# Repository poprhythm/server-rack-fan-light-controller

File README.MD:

# Server Rack Fan & Light Controller PCB
Provides control for server rack electronics using ESP32.

## Firmware

ESP32 firmware with temperature-controlled fans and MQTT monitoring is available in the [firmware/](./firmware/) directory.

PCB Mounted Components

- J1:	Front Connections - 8 pin Dupont connector
- J2:	Back Connections - 8 pin Dupont connector
- J3:	Barrel Jack for 24V
- J4:	[TMP32](https://www.amazon.com/dp/B08BFY91ZW)
- Q1, Q2:	[RFP30N06LE](https://www.digikey.com/en/products/detail/onsemi/RFP30N06LE/458769)
- R1, R2:	10K
- U1:	[ESP32 - ESP-WROOM-32 ESP-32S](https://www.amazon.com/ESP-WROOM-32-Development-Microcontroller-Integrated-Compatible/dp/B08D5ZD528)
- U2:	[LM2596S-Module 24V to 12V](https://www.amazon.com/dp/B076H3XHXP)
- U3:	[LM2596S-Module 24V to 5V](https://www.amazon.com/dp/B076H3XHXP)

External Components

- [24V LED Light strips](https://www.amazon.com/dp/B0D454HJ8G)
- [12V Fans](https://www.amazon.com/dp/B07HC782D5)
- [Door Sensor](https://www.amazon.com/dp/B0B3D7BM4K)
- [Electrical Wire](https://www.amazon.com/dp/B0CN76J8KR)
- [Dupont Connectors](https://www.amazon.com/dp/B078RRPRQZ)

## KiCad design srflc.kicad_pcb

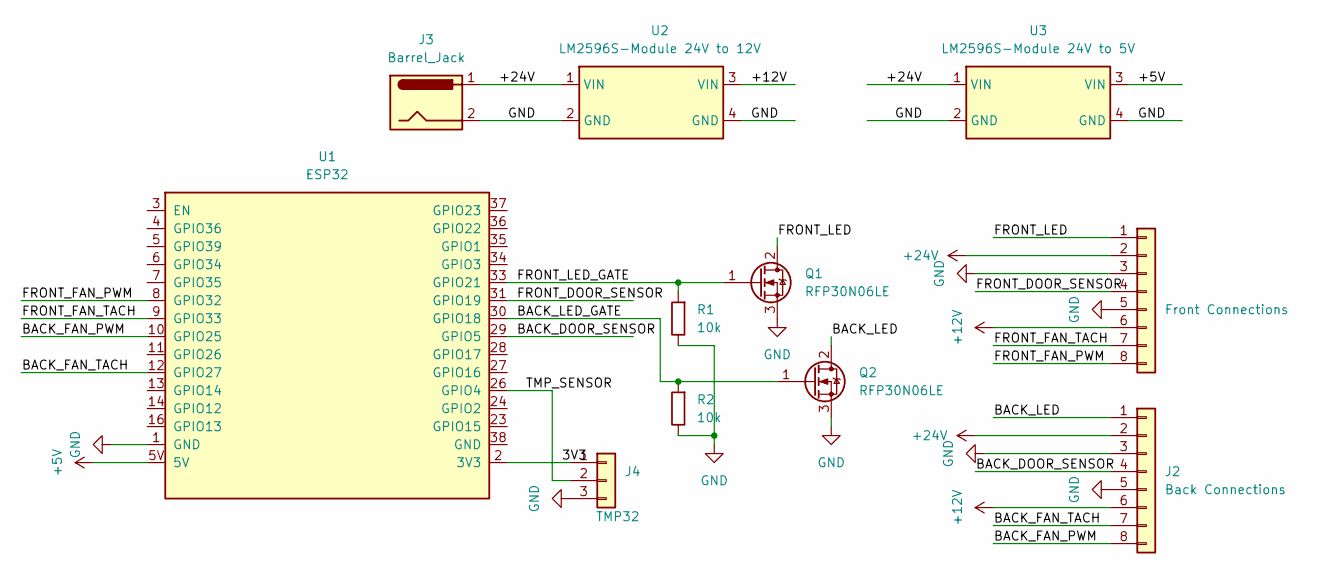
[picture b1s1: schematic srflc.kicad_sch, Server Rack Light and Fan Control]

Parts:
J1: Front Connections; PinHeader_1x08_P2.54mm_Horizontal
J2: Back Connections; PinHeader_1x08_P2.54mm_Horizontal
J3: Barrel_Jack; PinHeader_1x02_P2.54mm_Vertical
J4: TMP32; PinHeader_1x03_P2.54mm_Vertical
Q1, Q2: RFP30N06LE; PinHeader_1x03_P2.54mm_Vertical
R1, R2: 10k; R_Axial_DIN0207_L6.3mm_D2.5mm_P10.16mm_Horizontal
U1: ESP32; ESP32-C3-DevKitM-1
U2: LM2596S-Module 24V to 12V; LM2596 DC to DC High Efficiency Voltage Regulator 3.2-35V t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
U3: LM2596S-Module 24V to 5V; LM2596 DC to DC High Efficiency Voltage Regulator 3.2-35V t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

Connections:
+5V: U1.5V, U3.3 (VIN)
+12V: J1.6, J2.6, U2.3 (VIN)
+24V: J1.2, J2.2, J3.1, U2.1 (VIN), U3.1 (VIN)
/3V3: J4.1, U1.2 (3V3)
/BACK_DOOR_SENSOR: J2.4, U1.29 (GPIO5)
/BACK_FAN_PWM: J2.8, U1.10 (GPIO25)
/BACK_FAN_TACH: J2.7, U1.12 (GPIO27)
/BACK_LED: J2.1, Q2.2 (D)
/BACK_LED_GATE: Q2.1 (G), R2.1, U1.30 (GPIO18)
/FRONT_DOOR_SENSOR: J1.4, U1.31 (GPIO19)
/FRONT_FAN_PWM: J1.8, U1.8 (GPIO32)
/FRONT_FAN_TACH: J1.7, U1.9 (GPIO33)
/FRONT_LED: J1.1, Q1.2 (D)
/FRONT_LED_GATE: Q1.1 (G), R1.1, U1.33 (GPIO21)
/TMP_SENSOR: J4.2, U1.26 (GPIO4)
GND: J1.3, J1.5, J2.3, J2.5, J3.2, J4.3, Q1.3 (S), Q2.3 (S), R1.2, R2.2, U1.1 (GND), U2.2 (GND), U2.4 (GND), U3.2 (GND), U3.4 (GND)

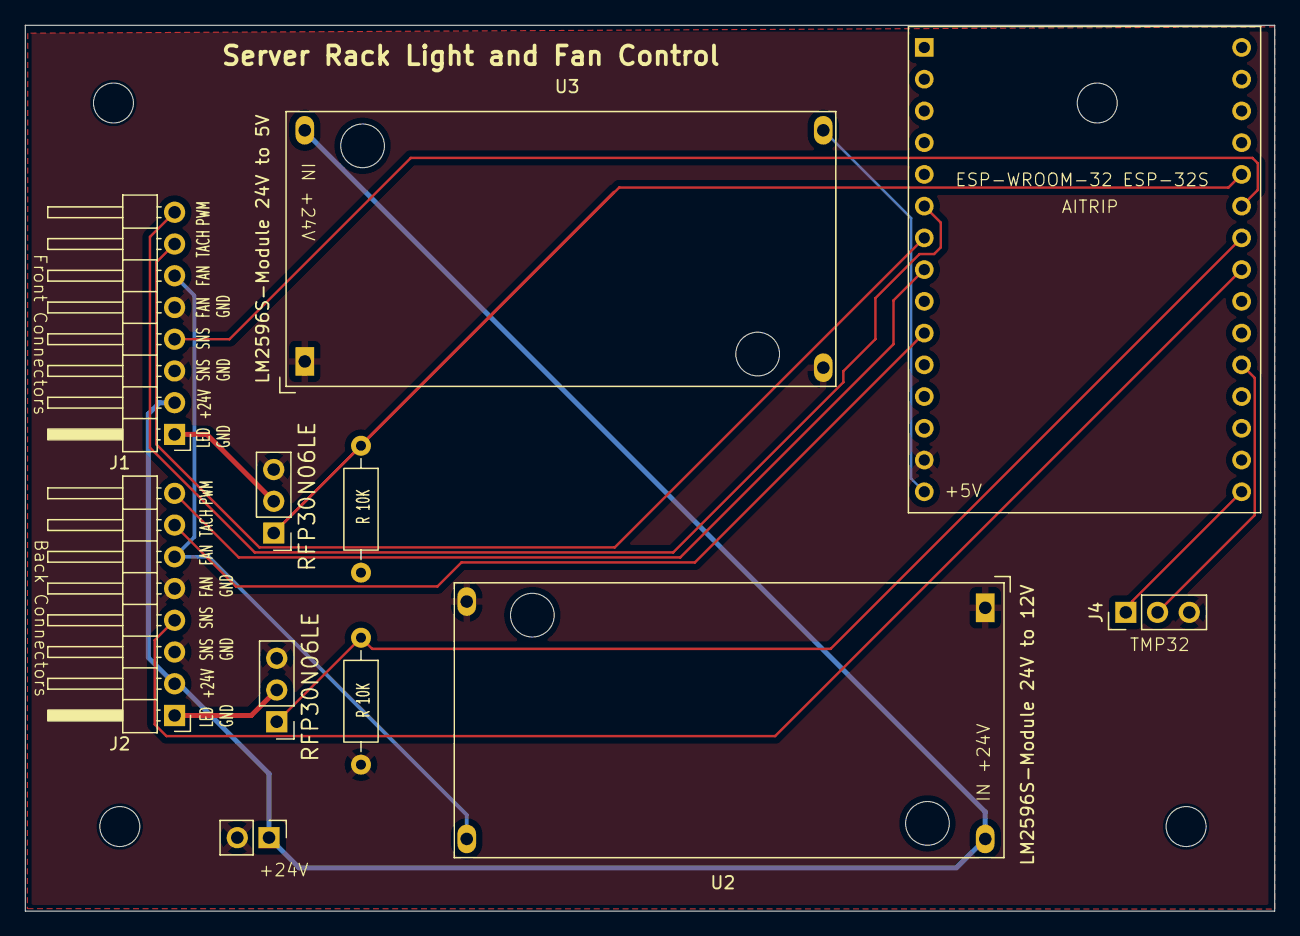
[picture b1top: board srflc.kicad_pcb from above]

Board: 2 copper layers, 100.0 x 70.9 mm, 11 parts (0 on the bottom side), 16 nets.

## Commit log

2025-10-29 Add images
2025-11-27 Add ESP32 firmware for fan and light controller
    Complete firmware implementation with the following features:
    Hardware Control:
    - Temperature-controlled fan speed (30-100%) using TMP36 sensor
    - Dual fan control with tachometer feedback
    - Door sensor monitoring with LED indicators
    - Temperature sensor validation with failsafe mode (runs fans at 100% on failure)
2025-12-03 Improvements
